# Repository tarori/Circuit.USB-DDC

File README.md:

This circuit is a USB to I2S converter.
* Firmware and further description is [here](https://github.com/tarori/Firmware.USB-DDC.git).
* [Latest version](https://github.com/tarori/Circuit.USB-DAC).
* .sch and .brd are EAGLE cad file.

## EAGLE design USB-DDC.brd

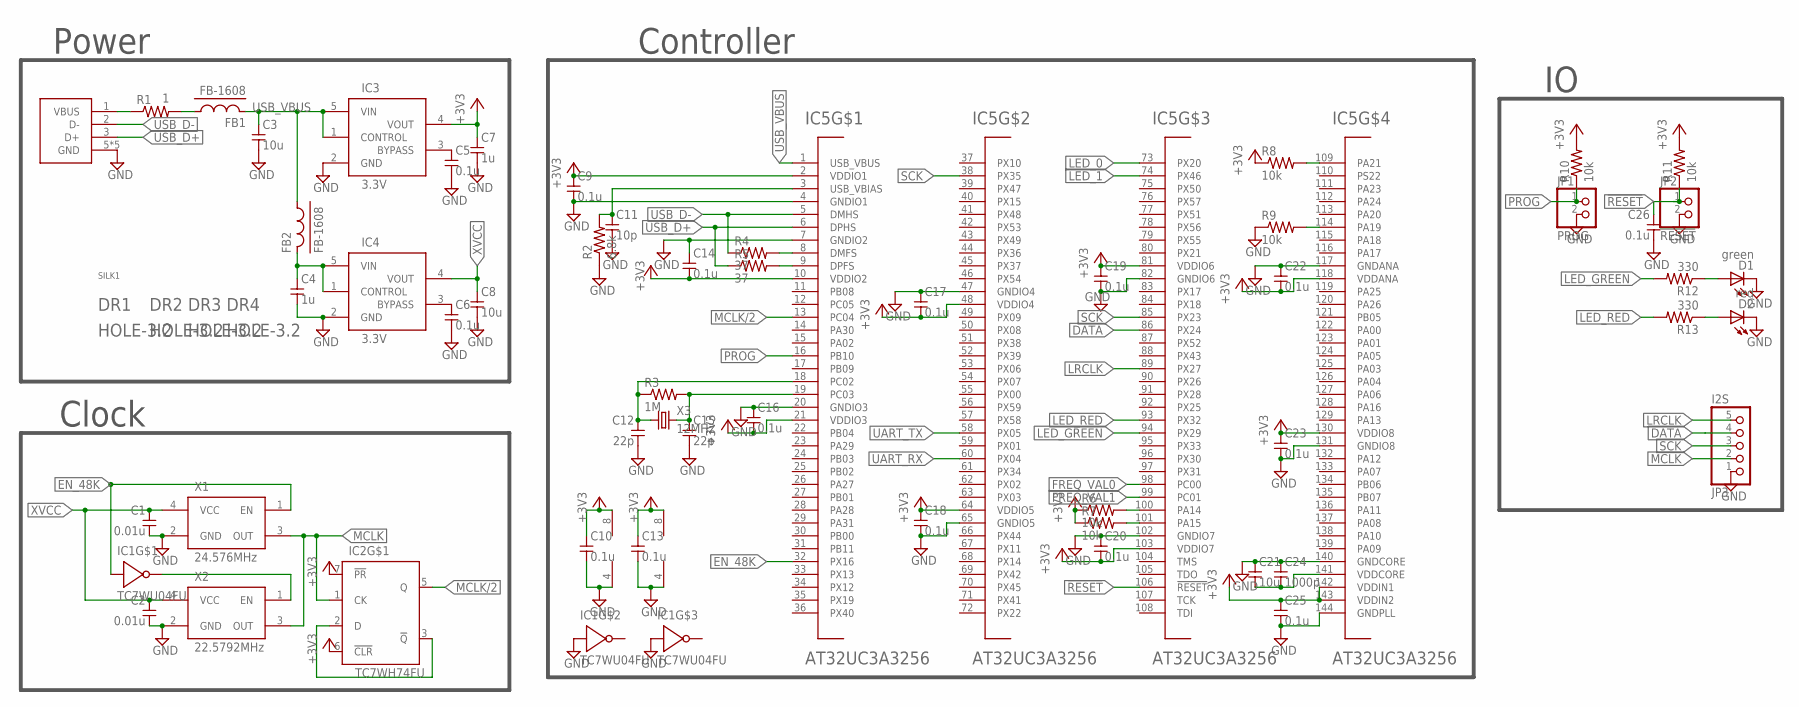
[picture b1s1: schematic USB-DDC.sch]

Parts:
C1, C2: 0.01u; 1608
C3, C8, C21: 10u; 2012
C4: 1u; 1608
C5, C6, C9, C10, C13, C14, C16, C17, C18, C19, C20, C22, C23, C25, C26: 0.1u; 1608
C7: 1u; 2012
C11: 10p; 1608
C12, C15: 22p; 1608
C24: 1000p; 1608
CON1: USB; UX60A-MB-5ST
D1: green; D1608
D2: red; D1608
DR1, DR2, DR3, DR4: HOLE-3.2; HOLE_3.2
FB1, FB2: FB-1608; 1608
IC1: TC7WU04FU; SSOP8-P-0.65
IC2: TC7WH74FU; SSOP8-P-0.65
IC3, IC4: 3.3V; SOT23-5
IC5: AT32UC3A3256; TQFP144
JP1: PROG; 1X02
JP2: !RESET; 1X02
JP3: I2S; 1X05
R1: 1; 0204/7
R2: 6.8k; 1608
R3: 1M; 0204/7
R4, R5: 37; 1608
R6, R7, R8, R9, R10, R11: 10k; 1608
R12, R13: 330; 1608
SILK1: ROBOTECHWHEELSILK-9MM; ROBOTECHWHEEL-9MM
X1: 24.576MHz; KC7050
X2: 22.5792MHz; KC7050
X3: 12MHz; HC49/S

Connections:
!RESET: C26.1, IC5.106 (!RESET), JP2.1, R11.1
+3V3: C7.1, C9.1, C10.1, C13.1, C14.2, C16.2, C17.2, C18.1, C19.1, C20.2, C22.2, C23.1, C25.1, IC1.8 (V+), IC2.6 (!CLR), IC2.7 (!PR), IC2.8 (V+), IC3.4 (VOUT), IC5.2 (VDDIO1), IC5.10 (VDDIO2), IC5.21 (VDDIO3), IC5.48 (VDDIO4), IC5.64 (VDDIO5), IC5.81 (VDDIO6), IC5.103 (VDDIO7), IC5.118 (VDDANA), IC5.130 (VDDIO8), IC5.142 (VDDIN1), IC5.143 (VDDIN2), R6.1, R7.1, R8.1, R10.2, R11.2
DATA: IC5.86 (PX24), JP3.4
EN_48K: IC1.1, IC5.32 (PX16), X1.1 (EN)
FREQ_VAL0: IC5.98 (PC00)
FREQ_VAL1: IC5.99 (PC01)
GND: C1.2, C2.2, C3.2, C4.2, C5.2, C6.2, C7.2, C8.2, C9.2, C10.2, C11.2, C12.2, C13.2, C14.1, C15.2, C16.1, C17.1, C18.2, C19.2, C20.1, C21.1, C22.1, C23.2, C24.1, C25.2, C26.2, CON1.5 (GND), CON1.M1 (GND), CON1.M2 (GND), CON1.M3 (GND), CON1.M4 (GND), D1.K, D2.K, IC1.3, IC1.4 (V-), IC1.6, IC2.4 (V-), IC3.2 (GND), IC4.2 (GND), IC5.4 (GNDIO1), IC5.7 (GNDIO2), IC5.20 (GNDIO3), IC5.47 (GNDIO4), IC5.65 (GNDIO5), IC5.82 (GNDIO6), IC5.102 (GNDIO7), IC5.117 (GNDANA), IC5.131 (GNDIO8), IC5.140 (GNDCORE), IC5.144 (GNDPLL), JP1.2, JP2.2, JP3.1, R2.1, R9.1, X1.2 (GND), X2.2 (GND)
LED_0: IC5.73 (PX20)
LED_1: IC5.74 (PX46)
LED_GREEN: IC5.94 (PX29), R12.2
LED_RED: IC5.93 (PX32), R13.2
LRCLK: IC5.89 (PX27), JP3.5
MCLK: IC2.1 (CK), JP3.2, X1.3 (OUT), X2.3 (OUT)
MCLK/2: IC2.5 (Q), IC5.13 (PC04)
unnamed: C5.1, IC3.3 (BYPASS)
unnamed: C6.1, IC4.3 (BYPASS)
unnamed: FB1.1, R1.2
unnamed: CON1.1 (VBUS), R1.1
unnamed: C4.1, FB2.2, IC4.1 (CONTROL), IC4.5 (VIN)
unnamed: C11.1, IC5.3 (USB_VBIAS), R2.2
unnamed: IC5.8 (DMFS), R4.2
unnamed: IC5.9 (DPFS), R5.2
unnamed: D2.A, R13.1
unnamed: C15.1, IC5.19 (PC03), R3.2, X3.2
unnamed: C12.1, IC5.18 (PC02), R3.1, X3.1
unnamed: IC1.7, X2.1 (EN)
unnamed: IC5.100 (PA14), R6.2
unnamed: IC5.101 (PA15), R7.2
unnamed: D1.A, R12.1
unnamed: C21.2, C24.2, IC5.141 (VDDCORE)
unnamed: IC2.2 (D), IC2.3 (!Q)
unnamed: IC5.109 (PA21), R8.2
unnamed: IC5.114 (PA19), R9.2
PROG: IC5.16 (PB10), JP1.1, R10.1
SCK: IC5.38 (PX35), IC5.85 (PX23), JP3.3
UART_RX: IC5.60 (PX04)
UART_TX: IC5.58 (PX05)
USB_D+: CON1.3 (D+), IC5.6 (DPHS), R5.1
USB_D-: CON1.2 (D-), IC5.5 (DMHS), R4.1
USB_VBUS: C3.1, FB1.2, FB2.1, IC3.1 (CONTROL), IC3.5 (VIN), IC5.1 (USB_VBUS)
XVCC: C1.1, C2.1, C8.1, IC4.4 (VOUT), X1.4 (VCC), X2.4 (VCC)

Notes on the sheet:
Power
Controller
Clock

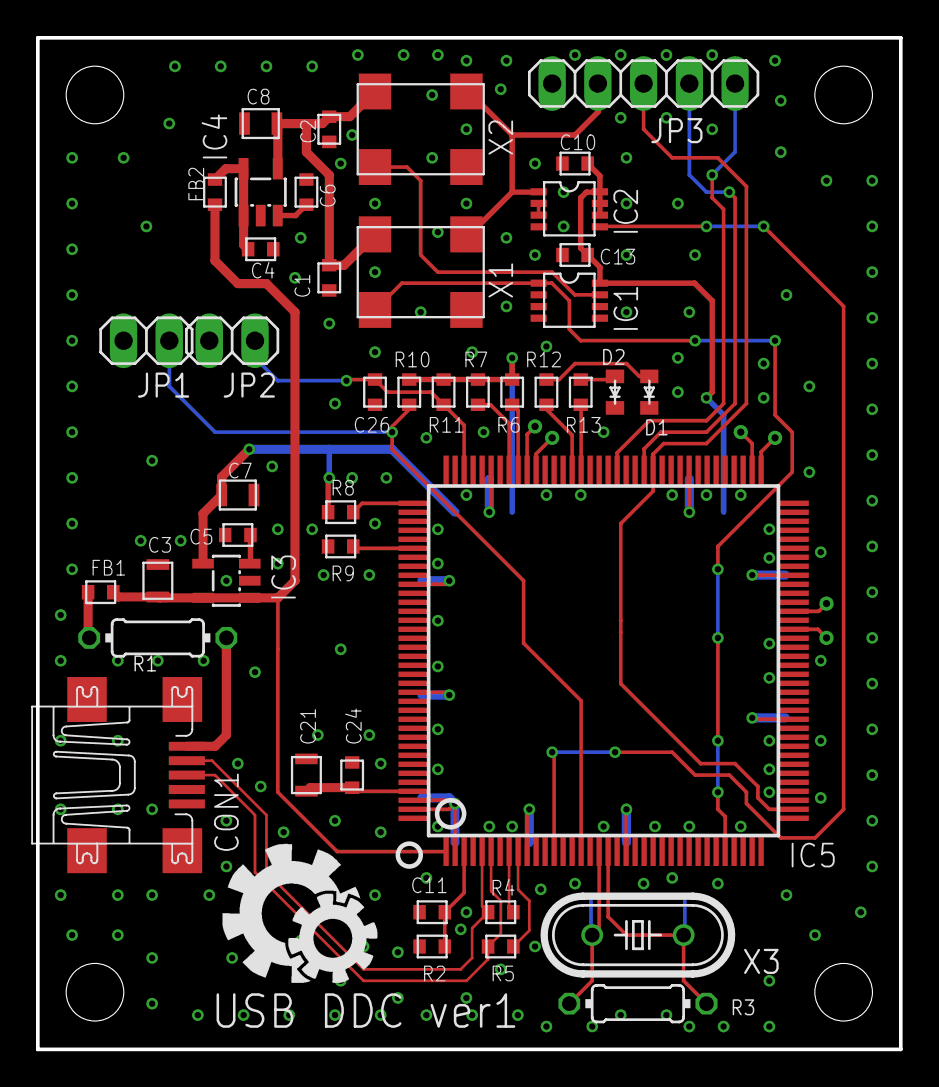
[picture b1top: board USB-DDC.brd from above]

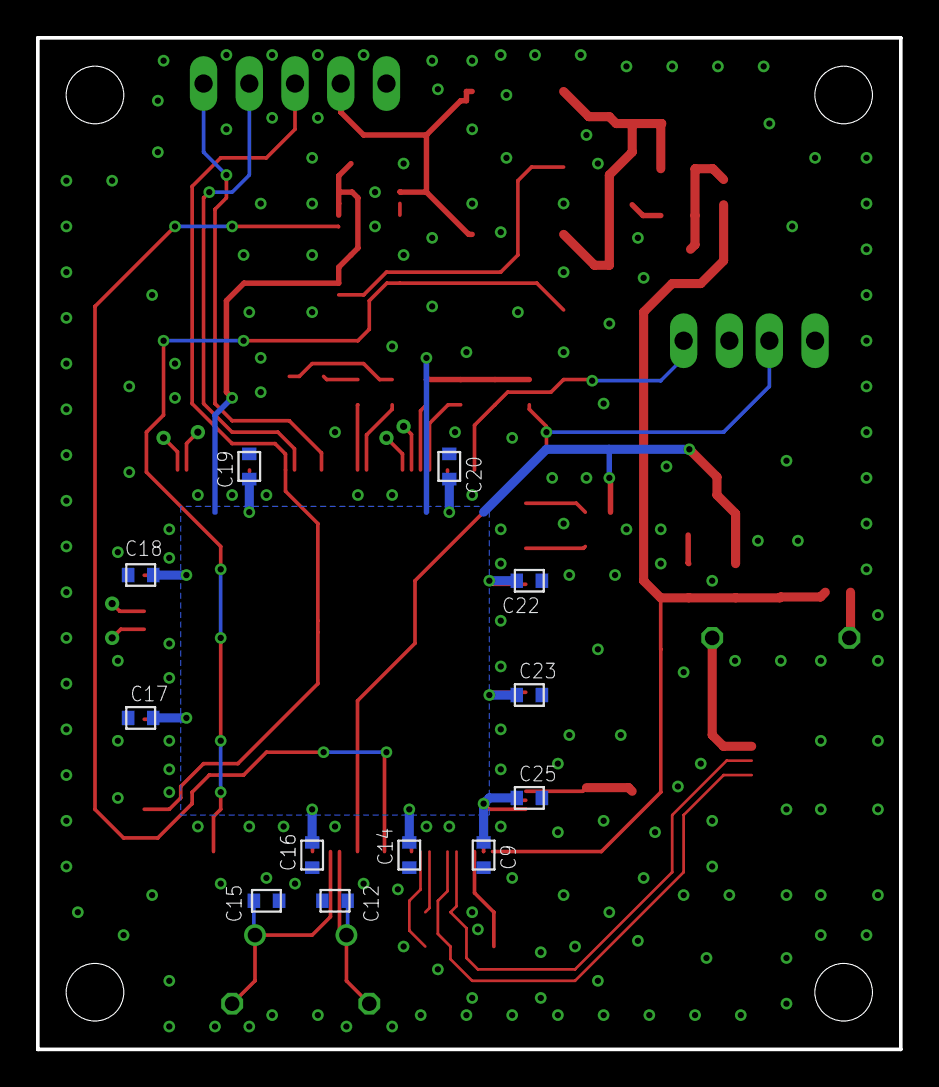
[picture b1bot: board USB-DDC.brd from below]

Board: 2 copper layers, 47.9 x 56.2 mm, 60 parts (12 on the bottom side), 35 nets.

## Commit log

2020-02-25 回路図完成
2020-03-11 Tiny fix
